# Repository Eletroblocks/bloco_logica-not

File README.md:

# logica-not
INVERTE o sinal de energia elétrica dos blocos seguintes, ligando blocos que estariam desligados e desligando blocos que estariam ligados.

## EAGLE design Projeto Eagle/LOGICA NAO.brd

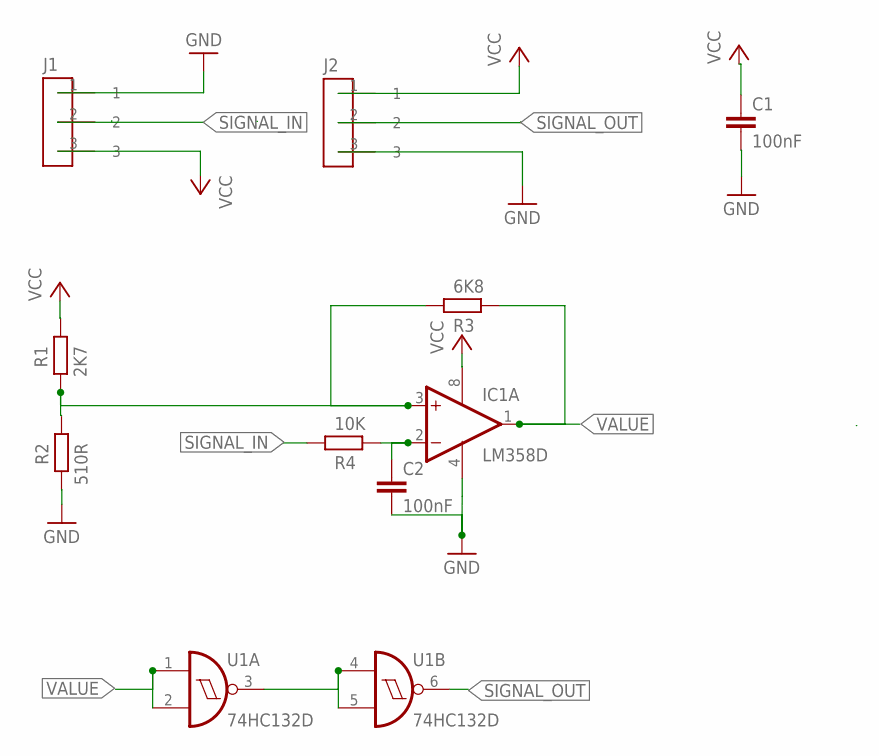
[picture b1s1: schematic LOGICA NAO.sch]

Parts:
C1, C2: 100nF; C0805
IC1: LM358D; SO08
J1: CONECTOR_MACHO; 3CONECTOR
J2: CONECTOR_FEMEA; 3CONECTOR
R1: 2K7; R0805W
R2: 510R; R0805W
R3: 6K8; R0805W
R4: 10K; R0805W
U1: 74HC132D; SO14

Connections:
GND: C1.2, C2.2, IC1.4 (V-), J1.1, J2.3, R2.2, U1.7 (GND)
unnamed: C2.1, IC1.2 (-IN), R4.2
unnamed: U1.3 (O), U1.4 (I0), U1.5 (I1)
unnamed: IC1.3 (+IN), R1.2, R2.1, R3.1
SIGNAL_IN: J1.2, R4.1
SIGNAL_OUT: J2.2, U1.6 (O)
VALUE: IC1.1 (OUT), R3.2, U1.1 (I0), U1.2 (I1)
VCC: C1.1, IC1.8 (V+), J1.3, J2.1, R1.1, U1.14 (VCC)

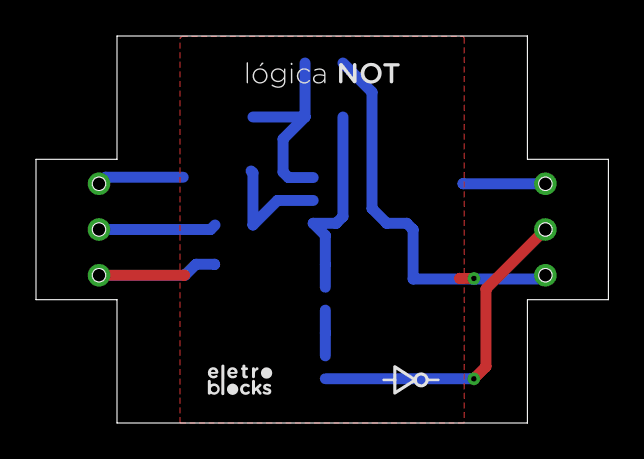
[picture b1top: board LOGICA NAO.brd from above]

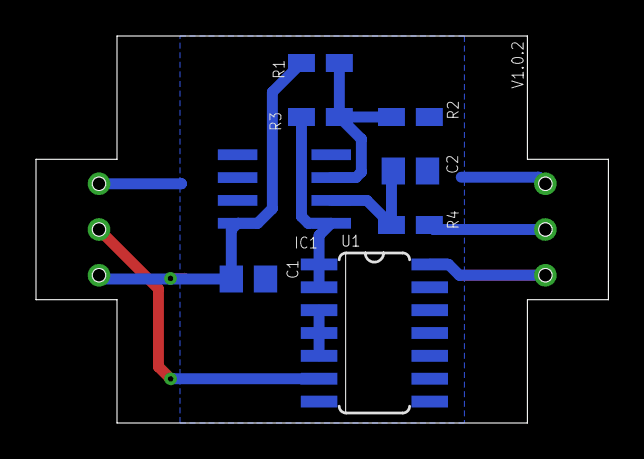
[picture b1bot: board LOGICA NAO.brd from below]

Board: 2 copper layers, 31.8 x 21.5 mm, 11 parts (8 on the bottom side), 8 nets.

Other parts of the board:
U$1: VERSAO

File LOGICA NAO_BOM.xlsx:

BOM LIST LOGICA NAO
DESCRIPTION | QUANTITY | POSITION | PART NUMBER
CAPACITOR 100nF 0805 | 2 | C1, C2 | UMF212B7104KGHT, can be replaced to similar
RESISTOR 2.7K 0805 | 1 | R1 | RT0805FRE072K7L, can be replaced to similar
RESISTOR 510R 0806 | 1 | R2 | RT0805FRE07510RL, can be replaced to similar
RESISTOR 6.8K 0807 | 1 | R3 | RT0805FRE076K8L, can be replaced to similar
RESISTOR 10K 0808 | 1 | R4 | RT0805FRE0710KL, can be replaced to similar
OPERACIONAL AMPLIFIER | 1 | IC1 | LM358BIDR
NAND SHCMITT TRIGGER | 1 | U1 | 74HC132D,653
MALE CONNECTOR | 1 | J1 | THIS COMPONENT IS PROVIDE BY ELETROBLOCKS
FEMALE CONNECTOR | 1 | J2 | THIS COMPONENT IS PROVIDE BY ELETROBLOCKS

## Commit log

2020-11-23 project init
2020-11-23 correção de pads e adição de label para versionamento
2020-11-23 correção de sensibilidade, reformulação de lógica, adição de plano VCC e atualização da BOM
2020-11-23 correção de label
2020-12-28 organizando arquivos
2020-12-28 imagem
